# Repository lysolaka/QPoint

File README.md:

# QPoint

This is a medicore BJT measurement device. It does not use SMUs, negative voltages, and other fancy things. The focus of this project was to learn analog circuits and use them in something (hopefully fun).

# License

This project is licensed under the GNU General Public License v3.0 or later (at your option).

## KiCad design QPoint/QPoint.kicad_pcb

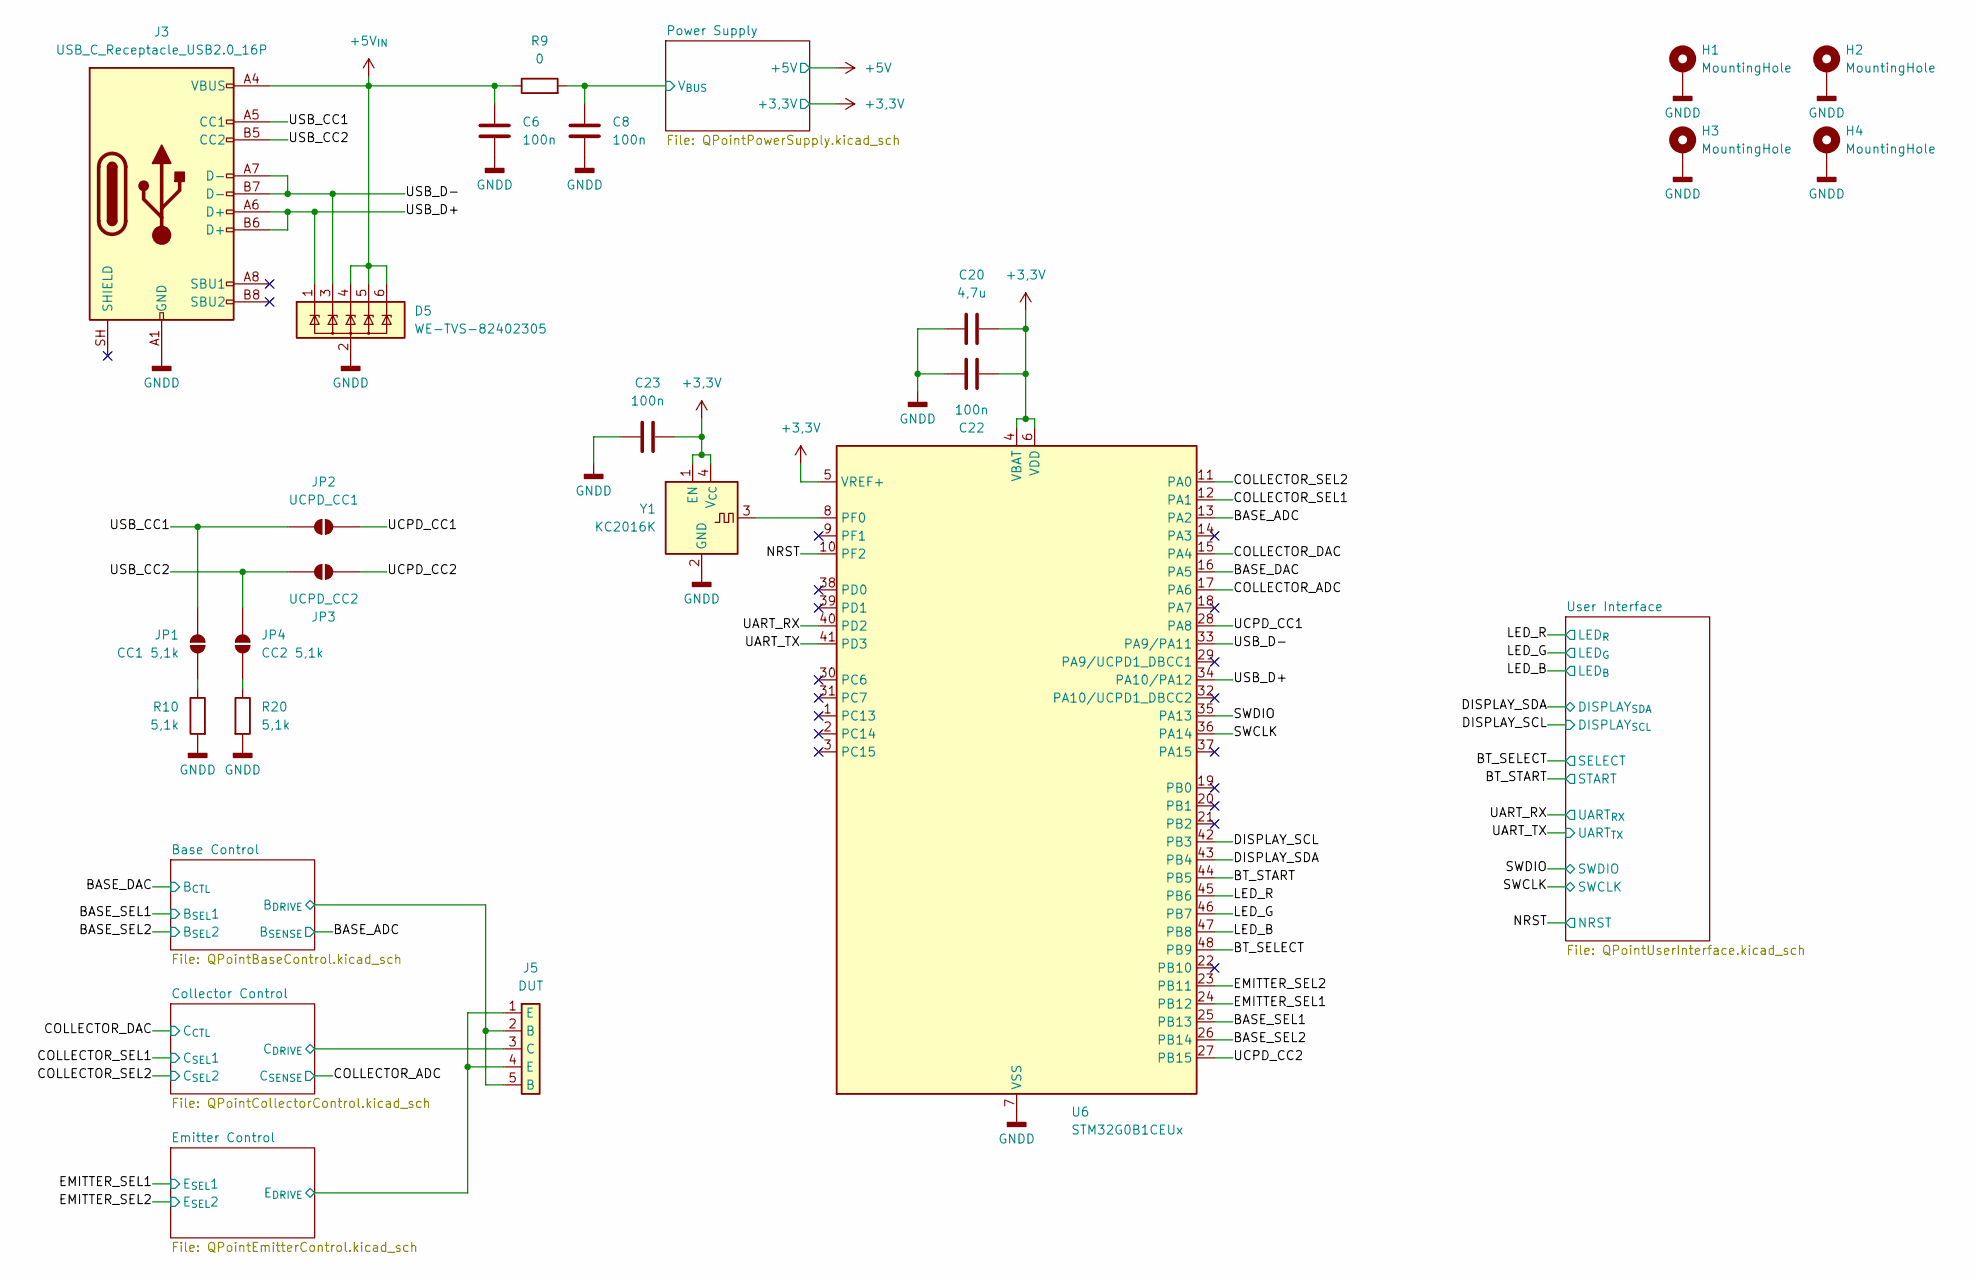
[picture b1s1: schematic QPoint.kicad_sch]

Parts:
C6, C8, C22, C23: 100n; C_0603_1608Metric_Pad1.08x0.95mm_HandSolder
C20: 4,7u; C_0805_2012Metric_Pad1.18x1.45mm_HandSolder
D5: WE-TVS-82402305; SOT-23-6_Handsoldering
H1, H2, H3, H4: MountingHole; MountingHole_3.2mm_M3_Pad
J3: USB_C_Receptacle_USB2.0_16P; USB_C_Receptacle_GCT_USB4085
J5: DUT; Connector_DUT_P2.54mm
JP1: CC1 5,1k; SolderJumper-2_P1.3mm_Open_TrianglePad1.0x1.5mm
JP2: UCPD_CC1; SolderJumper-2_P1.3mm_Open_TrianglePad1.0x1.5mm
JP3: UCPD_CC2; SolderJumper-2_P1.3mm_Open_TrianglePad1.0x1.5mm
JP4: CC2 5,1k; SolderJumper-2_P1.3mm_Open_TrianglePad1.0x1.5mm
R9: 0; R_0805_2012Metric_Pad1.20x1.40mm_HandSolder
R10, R20: 5,1k; R_0603_1608Metric_Pad0.98x0.95mm_HandSolder
U6: STM32G0B1CEUx; QFN-48-1EP_7x7mm_P0.5mm_EP5.6x5.6mm_GroundingVias
Y1: KC2016K; Oscillator_SMD_KC2016K_2.0x.16mm

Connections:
+3,3V: C20.2, C22.2, C23.2, U6.4 (VBAT), U6.5 (VREF+), U6.6 (VDD), Y1.1 (EN), Y1.4 (V_{CC}); also elsewhere on the board
+5V_{IN}: C6.1, D5.4, D5.5, D5.6, J3.A4 (VBUS), J3.A9 (VBUS), J3.B4 (VBUS), J3.B9 (VBUS), R9.1
/BASE_ADC: U6.13 (PA2); also elsewhere on the board
/BASE_DAC: U6.16 (PA5); also elsewhere on the board
/BASE_SEL1: U6.25 (PB13); also elsewhere on the board
/BASE_SEL2: U6.26 (PB14); also elsewhere on the board
/BT_SELECT: U6.48 (PB9); also elsewhere on the board
/BT_START: U6.44 (PB5); also elsewhere on the board
/Base Control/B_{DRIVE}: J5.2 (B), J5.5 (B); also elsewhere on the board
/COLLECTOR_ADC: U6.17 (PA6); also elsewhere on the board
/COLLECTOR_DAC: U6.15 (PA4); also elsewhere on the board
/COLLECTOR_SEL1: U6.12 (PA1); also elsewhere on the board
/COLLECTOR_SEL2: U6.11 (PA0); also elsewhere on the board
/Collector Control/C_{DRIVE}: J5.3 (C); also elsewhere on the board
/DISPLAY_SCL: U6.42 (PB3); also elsewhere on the board
/DISPLAY_SDA: U6.43 (PB4); also elsewhere on the board
/EMITTER_SEL1: U6.24 (PB12); also elsewhere on the board
/EMITTER_SEL2: U6.23 (PB11); also elsewhere on the board
/Emitter Control/E_{DRIVE}: J5.1 (E), J5.4 (E); also elsewhere on the board
/LED_B: U6.47 (PB8); also elsewhere on the board
/LED_G: U6.46 (PB7); also elsewhere on the board
/LED_R: U6.45 (PB6); also elsewhere on the board
/NRST: U6.10 (PF2); also elsewhere on the board
/Power Supply/V_{BUS}: C8.1, R9.2; also elsewhere on the board
/SWCLK: U6.36 (PA14); also elsewhere on the board
/SWDIO: U6.35 (PA13); also elsewhere on the board
/UART_RX: U6.40 (PD2); also elsewhere on the board
/UART_TX: U6.41 (PD3); also elsewhere on the board
/UCPD_CC1: JP2.2 (B), U6.28 (PA8)
/UCPD_CC2: JP3.2 (B), U6.27 (PB15)
/USB_CC1: J3.A5 (CC1), JP1.1 (A), JP2.1 (A)
/USB_CC2: J3.B5 (CC2), JP3.1 (A), JP4.1 (A)
/USB_D+: D5.1, J3.A6 (D+), J3.B6 (D+), U6.34 (PA10/PA12)
/USB_D-: D5.3, J3.A7 (D-), J3.B7 (D-), U6.33 (PA9/PA11)
GNDD: C6.2, C8.2, C20.1, C22.1, C23.1, D5.2, H1.1 (1_1), H2.1 (1_1), H3.1 (1_1), H4.1 (1_1), J3.A1 (GND), J3.A12 (GND), J3.B1 (GND), J3.B12 (GND), R10.2, R20.2, U6.7 (VSS), U6.49 (VSS), Y1.2 (GND); also elsewhere on the board
unnamed: JP1.2 (B), R10.1
unnamed: JP4.2 (B), R20.1
unnamed: U6.8 (PF0), Y1.3

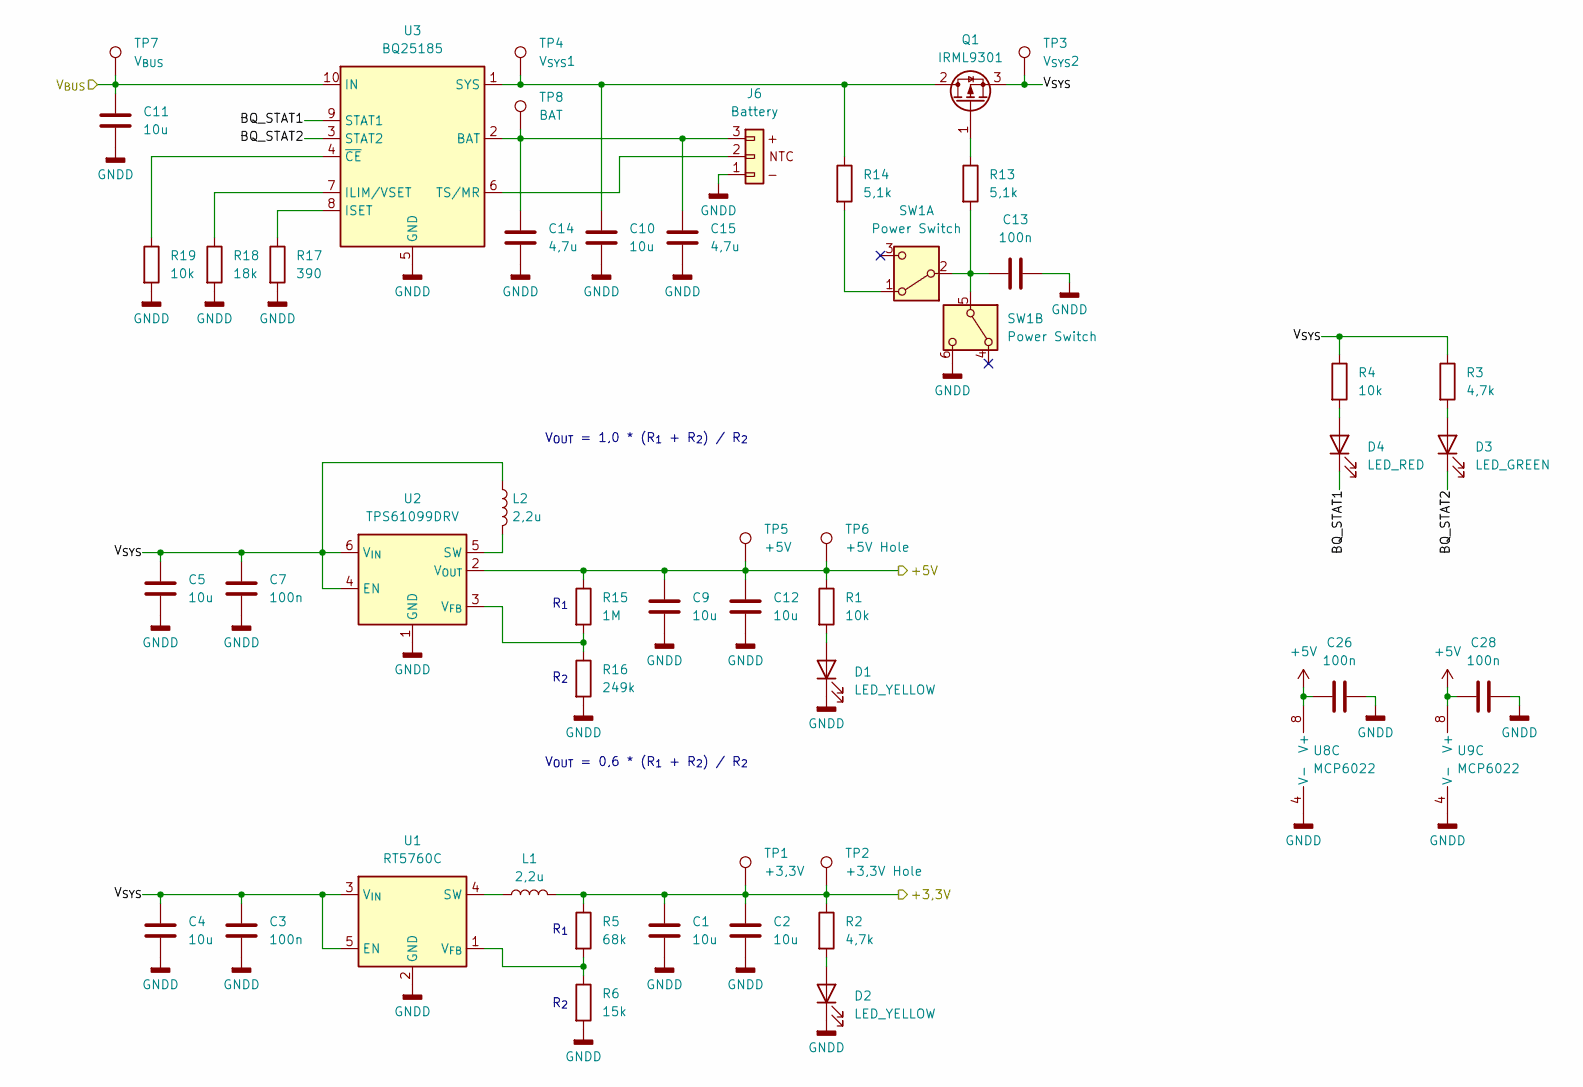
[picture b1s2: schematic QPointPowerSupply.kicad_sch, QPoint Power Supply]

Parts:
C1, C2, C4, C5, C9, C10, C11, C12: 10u; C_0805_2012Metric_Pad1.18x1.45mm_HandSolder
C3, C7, C13, C26, C28: 100n; C_0603_1608Metric_Pad1.08x0.95mm_HandSolder
C14, C15: 4,7u; C_0805_2012Metric_Pad1.18x1.45mm_HandSolder
D1, D2: LED_YELLOW; LED_0805_2012Metric_Pad1.15x1.40mm_HandSolder
D3: LED_GREEN; LED_0805_2012Metric_Pad1.15x1.40mm_HandSolder
D4: LED_RED; LED_0805_2012Metric_Pad1.15x1.40mm_HandSolder
J6: Battery; Molex_PicoBlade_53048-0310_1x03_P1.25mm_Horizontal
L1, L2: 2,2u; L_Sunlord_MWSA0503S
Q1: IRML9301; SOT-23_Handsoldering
R1, R4, R19: 10k; R_0603_1608Metric_Pad0.98x0.95mm_HandSolder
R2, R3: 4,7k; R_0603_1608Metric_Pad0.98x0.95mm_HandSolder
R5: 68k; R_0603_1608Metric_Pad0.98x0.95mm_HandSolder
R6: 15k; R_0603_1608Metric_Pad0.98x0.95mm_HandSolder
R13, R14: 5,1k; R_0603_1608Metric_Pad0.98x0.95mm_HandSolder
R15: 1M; R_0603_1608Metric_Pad0.98x0.95mm_HandSolder
R16: 249k; R_0603_1608Metric_Pad0.98x0.95mm_HandSolder
R17: 390; R_0603_1608Metric_Pad0.98x0.95mm_HandSolder
R18: 18k; R_0603_1608Metric_Pad0.98x0.95mm_HandSolder
SW1: Power Switch; SW_Push_PB07_7x7mm
TP1: +3,3V; TestPoint_Pad_D2.0mm
TP2: +3,3V Hole; TestPoint_THTPad_D2.0mm_Drill1.0mm
TP3: V_{SYS}2; TestPoint_Pad_D2.0mm
TP4: V_{SYS}1; TestPoint_Pad_D2.0mm
TP5: +5V; TestPoint_Pad_D2.0mm
TP6: +5V Hole; TestPoint_THTPad_D2.0mm_Drill1.0mm
TP7: V_{BUS}; TestPoint_Pad_D2.0mm
TP8: BAT; TestPoint_Pad_D2.0mm
U1: RT5760C; SOT-563_Handsoldering
U2: TPS61099DRV; WSON-6-1EP_2x2mm_P0.65mm_EP1x1.6mm_GroundingVias
U3: BQ25185; Texas_DLH0010A_WSON-10-1EP_2.2x2mm_P0.4mm_EP0.9x1.5mm_Groun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
U8, U9: MCP6022; SOIC-8_3.9x4.9mm_P1.27mm_Handsoldering

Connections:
+3,3V: C1.1, C2.1, L1.2, R2.1, R5.1, TP1.1 (1_1), TP2.1 (1_1); also elsewhere on the board
+5V: C9.1, C12.1, C26.1, C28.1, R1.1, R15.1, TP5.1 (1_1), TP6.1 (1_1), U2.2 (V_{OUT}), U8.8 (V+), U9.8 (V+); also elsewhere on the board
/Power Supply/BQ_STAT1: D4.1 (K), U3.9 (STAT1)
/Power Supply/BQ_STAT2: D3.1 (K), U3.3 (STAT2)
/Power Supply/V_{BUS}: C11.1, TP7.1 (1_1), U3.10 (IN); also elsewhere on the board
/Power Supply/V_{SYS}: C3.1, C4.1, C5.1, C7.1, L2.1, Q1.3 (S), R3.1, R4.1, TP3.1 (1_1), U1.3 (V_{IN}), U1.5 (EN), U2.4 (EN), U2.6 (V_{IN})
GNDD: C1.2, C2.2, C3.2, C4.2, C5.2, C7.2, C9.2, C10.2, C11.2, C12.2, C13.2, C14.2, C15.2, C26.2, C28.2, D1.1 (K), D2.1 (K), J6.1, R6.2, R16.2, R17.2, R18.2, R19.2, SW1.6 (C), U1.2 (GND), U2.1 (GND), U2.7 (GND), U3.5 (GND), U3.11 (TP), U8.4 (V-), U9.4 (V-); also elsewhere on the board
unnamed: D1.2 (A), R1.2
unnamed: D2.2 (A), R2.2
unnamed: D3.2 (A), R3.2
unnamed: D4.2 (A), R4.2
unnamed: C10.1, Q1.2 (D), R14.1, TP4.1 (1_1), U3.1 (SYS)
unnamed: Q1.1 (G), R13.1
unnamed: R14.2, SW1.1 (A)
unnamed: C13.1, R13.2, SW1.2 (B), SW1.5 (B)
unnamed: L1.1, U1.4 (SW)
unnamed: R5.2, R6.1, U1.1 (V_{FB})
unnamed: L2.2, U2.5 (SW)
unnamed: R15.2, R16.1, U2.3 (V_{FB})
unnamed: C14.1, C15.1, J6.3, TP8.1 (1_1), U3.2 (BAT)
unnamed: R18.1, U3.7 (ILIM/VSET)
unnamed: R17.1, U3.8 (ISET)
unnamed: J6.2, U3.6 (TS/MR)
unnamed: R19.1, U3.4 (~CE)

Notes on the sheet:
R_{2}
V_{OUT} = 0,6 * (R_{1} + R_{2}) / R_{2}
R_{1}
V_{OUT} = 1,0 * (R_{1} + R_{2}) / R_{2}

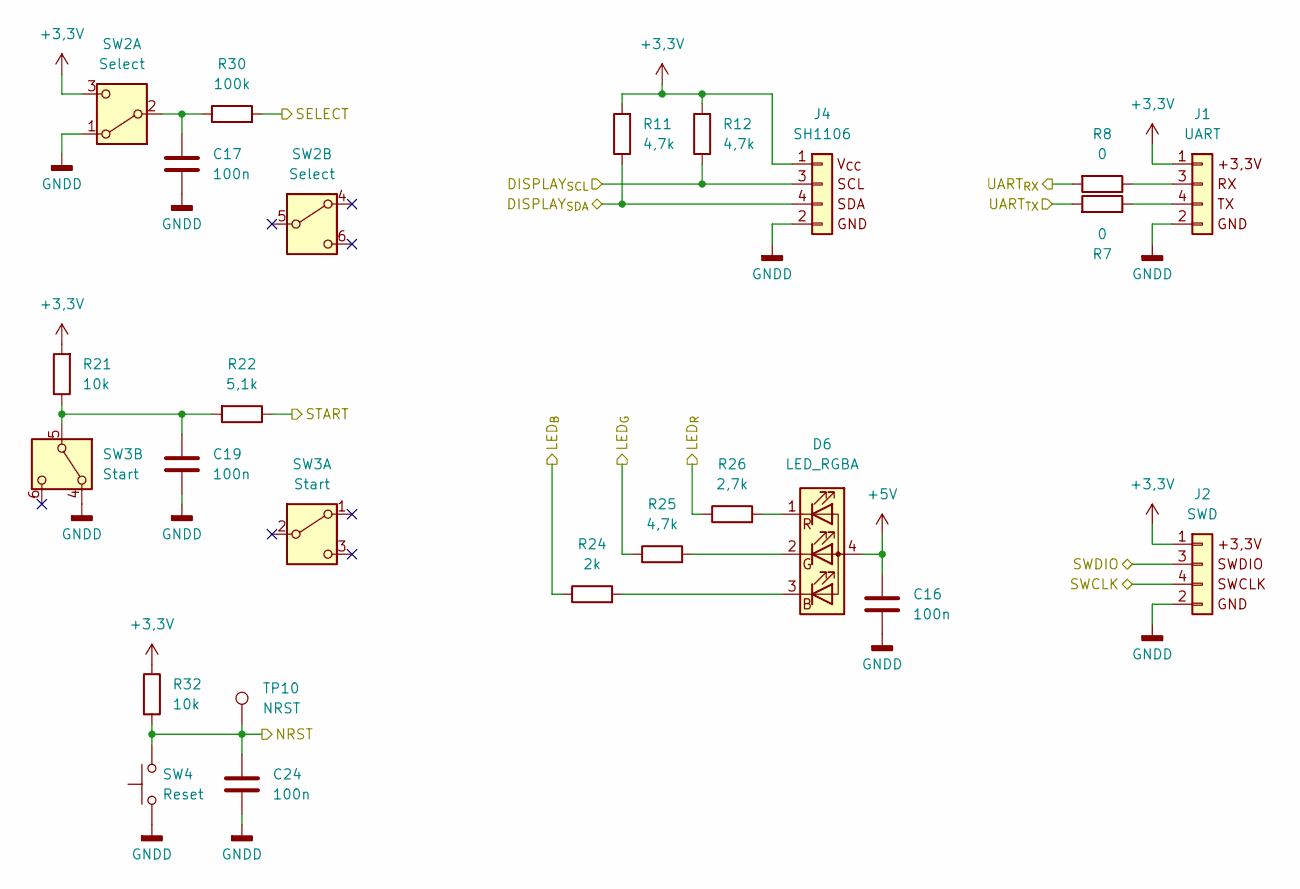
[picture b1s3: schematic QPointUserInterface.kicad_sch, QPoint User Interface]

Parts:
C16, C17, C19, C24: 100n; C_0603_1608Metric_Pad1.08x0.95mm_HandSolder
D6: LED_RGBA; LED_LiteOn_LTST-C19HE1WT
J1: UART; Connector_UART_P2.54mm
J2: SWD; Connector_SWD_P2.54mm
J4: SH1106; Connector_SH1106_P2.54mm
R7, R8: 0; R_0805_2012Metric_Pad1.20x1.40mm_HandSolder
R11, R12, R25: 4,7k; R_0603_1608Metric_Pad0.98x0.95mm_HandSolder
R21, R32: 10k; R_0603_1608Metric_Pad0.98x0.95mm_HandSolder
R22: 5,1k; R_0603_1608Metric_Pad0.98x0.95mm_HandSolder
R24: 2k; R_0603_1608Metric_Pad0.98x0.95mm_HandSolder
R26: 2,7k; R_0603_1608Metric_Pad0.98x0.95mm_HandSolder
R30: 100k; R_0603_1608Metric_Pad0.98x0.95mm_HandSolder
SW2: Select; SW_Push_PB07_7x7mm
SW3: Start; SW_Push_PB07_7x7mm
SW4: Reset; SW_Push_SPST_China
TP10: NRST; TestPoint_THTPad_D2.0mm_Drill1.0mm

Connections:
+3,3V: J1.1, J2.1, J4.1, R11.2, R12.2, R21.2, R32.1, SW2.3 (C); also elsewhere on the board
+5V: C16.1, D6.4 (A); also elsewhere on the board
/BT_SELECT: R30.2; also elsewhere on the board
/BT_START: R22.1; also elsewhere on the board
/DISPLAY_SCL: J4.3, R12.1; also elsewhere on the board
/DISPLAY_SDA: J4.4, R11.1; also elsewhere on the board
/LED_B: R24.1; also elsewhere on the board
/LED_G: R25.1; also elsewhere on the board
/LED_R: R26.1; also elsewhere on the board
/NRST: C24.1, R32.2, SW4.2, TP10.1 (1_1); also elsewhere on the board
/SWCLK: J2.4; also elsewhere on the board
/SWDIO: J2.3; also elsewhere on the board
/UART_RX: R8.2; also elsewhere on the board
/UART_TX: R7.2; also elsewhere on the board
GNDD: C16.2, C17.2, C19.2, C24.2, J1.2, J2.2, J4.2, SW2.1 (A), SW3.4 (A), SW4.1; also elsewhere on the board
unnamed: D6.3 (BK), R24.2
unnamed: D6.2 (GK), R25.2
unnamed: D6.1 (RK), R26.2
unnamed: J1.3, R8.1
unnamed: J1.4, R7.1
unnamed: C17.1, R30.1, SW2.2 (B)
unnamed: C19.1, R21.1, R22.2, SW3.5 (B)

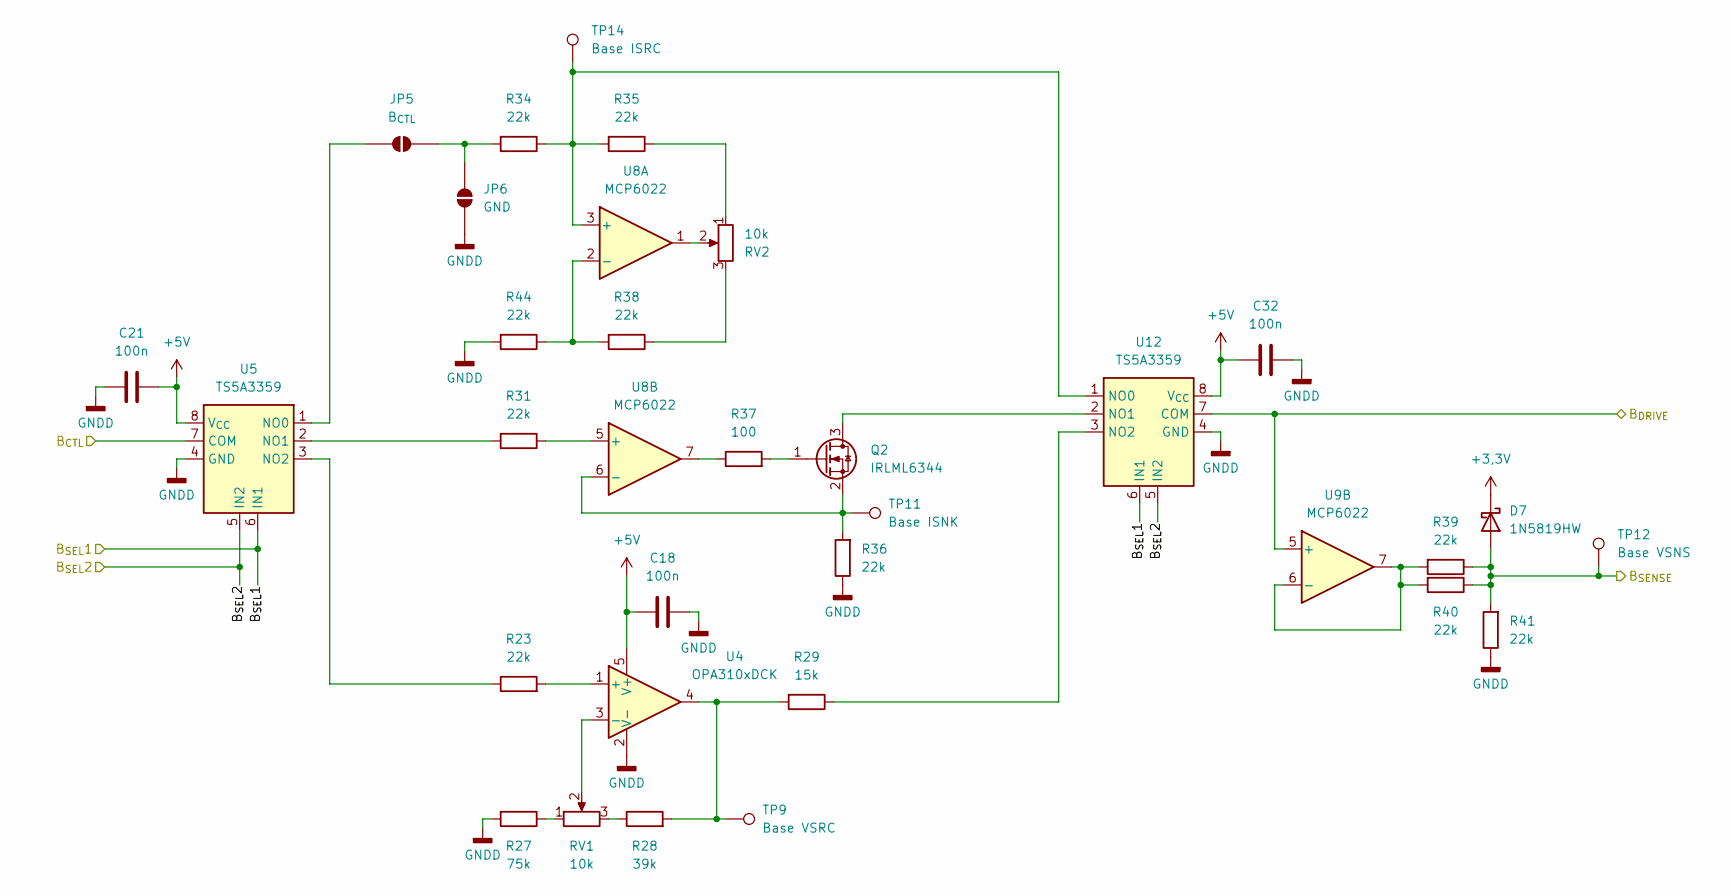
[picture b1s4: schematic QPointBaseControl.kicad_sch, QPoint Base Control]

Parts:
C18, C21, C32: 100n; C_0603_1608Metric_Pad1.08x0.95mm_HandSolder
D7: 1N5819HW; D_SOD-123_Handsoldering
JP5: B_{CTL}; SolderJumper-2_P1.3mm_Open_TrianglePad1.0x1.5mm
JP6: GND; SolderJumper-2_P1.3mm_Open_TrianglePad1.0x1.5mm
Q2: IRLML6344; SOT-23_Handsoldering
R23, R31, R34, R35, R36, R38, R39, R40, R41, R44: 22k; R_0603_1608Metric_Pad0.98x0.95mm_HandSolder
R27: 75k; R_0603_1608Metric_Pad0.98x0.95mm_HandSolder
R28: 39k; R_0603_1608Metric_Pad0.98x0.95mm_HandSolder
R29: 15k; R_0603_1608Metric_Pad0.98x0.95mm_HandSolder
R37: 100; R_0603_1608Metric_Pad0.98x0.95mm_HandSolder
RV1, RV2: 10k; Potentiometer_Bourns_3296X_Horizontal
TP9: Base VSRC; TestPoint_Pad_D2.0mm
TP11: Base ISNK; TestPoint_Pad_D2.0mm
TP12: Base VSNS; TestPoint_Pad_D2.0mm
TP14: Base ISRC; TestPoint_Pad_D2.0mm
U4: OPA310xDCK; SOT-353_SC-70-5_Handsoldering
U5, U12: TS5A3359; VSSOP-8_2.3x2mm_P0.5mm_Handsoldering
U8, U9: MCP6022; SOIC-8_3.9x4.9mm_P1.27mm_Handsoldering

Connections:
+3,3V: D7.1 (K); also elsewhere on the board
+5V: C18.1, C21.2, C32.2, U4.5 (V+), U5.8 (V_{CC}), U12.8 (V_{CC}); also elsewhere on the board
/BASE_ADC: D7.2 (A), R39.1, R40.1, R41.2, TP12.1 (1_1); also elsewhere on the board
/BASE_DAC: U5.7 (COM); also elsewhere on the board
/BASE_SEL1: U5.6 (IN1), U12.6 (IN1); also elsewhere on the board
/BASE_SEL2: U5.5 (IN2), U12.5 (IN2); also elsewhere on the board
/Base Control/B_{DRIVE}: U9.5 (+), U12.7 (COM); also elsewhere on the board
GNDD: C18.2, C21.1, C32.1, JP6.1 (A), R27.2, R36.1, R41.1, R44.2, U4.2 (V-), U5.4 (GND), U12.4 (GND); also elsewhere on the board
unnamed: JP5.1 (A), U5.1 (NO0)
unnamed: JP5.2 (B), JP6.2 (B), R34.2
unnamed: Q2.3 (D), U12.2 (NO1)
unnamed: Q2.1 (G), R37.2
unnamed: Q2.2 (S), R36.2, TP11.1 (1_1), U8.6 (-)
unnamed: R27.1, RV1.1
unnamed: R28.1, RV1.3
unnamed: R28.2, R29.2, TP9.1 (1_1), U4.4
unnamed: R35.1, RV2.1
unnamed: R37.1, U8.7
unnamed: R38.1, RV2.3
unnamed: RV2.2, U8.1
unnamed: R23.2, U4.1 (+)
unnamed: RV1.2, U4.3 (-)
unnamed: R31.2, U5.2 (NO1)
unnamed: R23.1, U5.3 (NO2)
unnamed: R38.2, R44.1, U8.2 (-)
unnamed: R31.1, U8.5 (+)
unnamed: R39.2, R40.2, U9.6 (-), U9.7
unnamed: R34.1, R35.2, TP14.1 (1_1), U8.3 (+), U12.1 (NO0)
unnamed: R29.1, U12.3 (NO2)

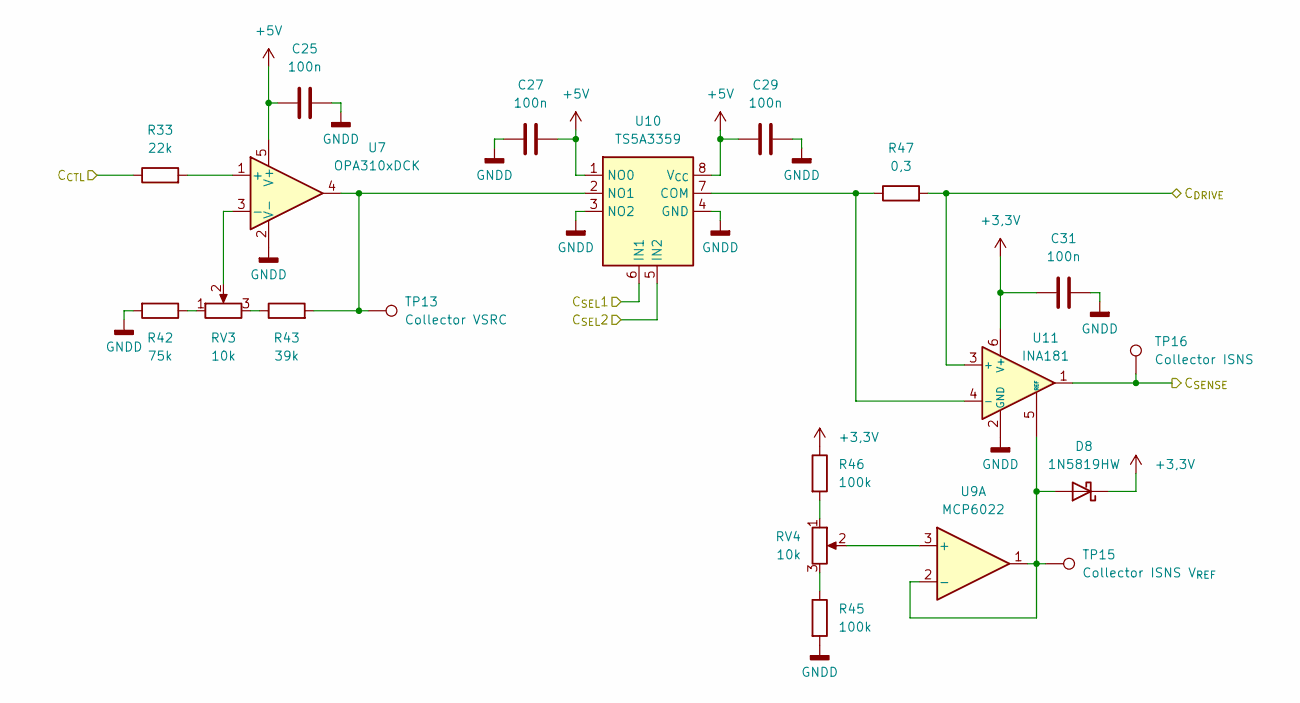
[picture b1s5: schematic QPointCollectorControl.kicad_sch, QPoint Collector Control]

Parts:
C25, C27, C29, C31: 100n; C_0603_1608Metric_Pad1.08x0.95mm_HandSolder
D8: 1N5819HW; D_SOD-123_Handsoldering
R33: 22k; R_0603_1608Metric_Pad0.98x0.95mm_HandSolder
R42: 75k; R_0603_1608Metric_Pad0.98x0.95mm_HandSolder
R43: 39k; R_0603_1608Metric_Pad0.98x0.95mm_HandSolder
R45, R46: 100k; R_0603_1608Metric_Pad0.98x0.95mm_HandSolder
R47: 0,3; R_0805_2012Metric_Pad1.20x1.40mm_HandSolder
RV3, RV4: 10k; Potentiometer_Bourns_3296X_Horizontal
TP13: Collector VSRC; TestPoint_Pad_D2.0mm
TP15: Collector ISNS V_{REF}; TestPoint_Pad_D2.0mm
TP16: Collector ISNS; TestPoint_Pad_D2.0mm
U7: OPA310xDCK; SOT-353_SC-70-5_Handsoldering
U9: MCP6022; SOIC-8_3.9x4.9mm_P1.27mm_Handsoldering
U10: TS5A3359; VSSOP-8_2.3x2mm_P0.5mm_Handsoldering
U11: INA181; SOT-23-6_Handsoldering

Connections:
+3,3V: C31.2, D8.1 (K), R46.1, U11.6 (V+); also elsewhere on the board
+5V: C25.1, C27.2, C29.2, U7.5 (V+), U10.1 (NO0), U10.8 (V_{CC}); also elsewhere on the board
/COLLECTOR_ADC: TP16.1 (1_1), U11.1; also elsewhere on the board
/COLLECTOR_DAC: R33.1; also elsewhere on the board
/COLLECTOR_SEL1: U10.6 (IN1); also elsewhere on the board
/COLLECTOR_SEL2: U10.5 (IN2); also elsewhere on the board
/Collector Control/C_{DRIVE}: R47.2, U11.3 (+); also elsewhere on the board
GNDD: C25.2, C27.1, C29.1, C31.1, R42.2, R45.2, U7.2 (V-), U10.3 (NO2), U10.4 (GND), U11.2 (GND); also elsewhere on the board
unnamed: D8.2 (A), TP15.1 (1_1), U9.1, U9.2 (-), U11.5 (REF)
unnamed: R42.1, RV3.1
unnamed: R43.1, RV3.3
unnamed: R45.1, RV4.3
unnamed: R46.2, RV4.1
unnamed: R33.2, U7.1 (+)
unnamed: RV3.2, U7.3 (-)
unnamed: RV4.2, U9.3 (+)
unnamed: R47.1, U10.7 (COM), U11.4 (-)
unnamed: R43.2, TP13.1 (1_1), U7.4, U10.2 (NO1)

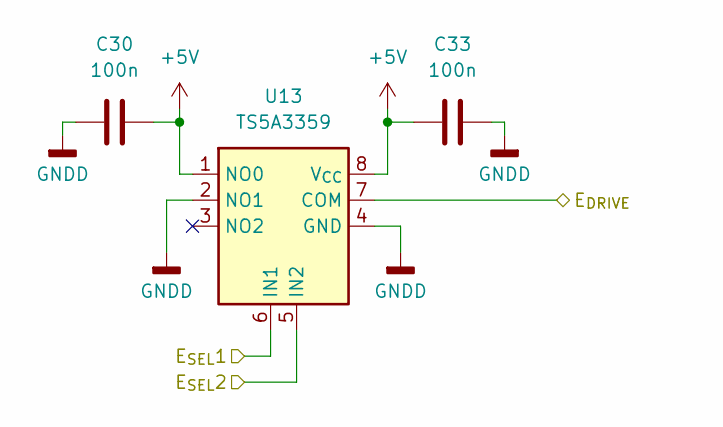
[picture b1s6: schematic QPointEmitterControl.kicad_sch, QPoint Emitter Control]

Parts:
C30, C33: 100n; C_0603_1608Metric_Pad1.08x0.95mm_HandSolder
U13: TS5A3359; VSSOP-8_2.3x2mm_P0.5mm_Handsoldering

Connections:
+5V: C30.2, C33.2, U13.1 (NO0), U13.8 (V_{CC}); also elsewhere on the board
/EMITTER_SEL1: U13.6 (IN1); also elsewhere on the board
/EMITTER_SEL2: U13.5 (IN2); also elsewhere on the board
/Emitter Control/E_{DRIVE}: U13.7 (COM); also elsewhere on the board
GNDD: C30.1, C33.1, U13.2 (NO1), U13.4 (GND); also elsewhere on the board

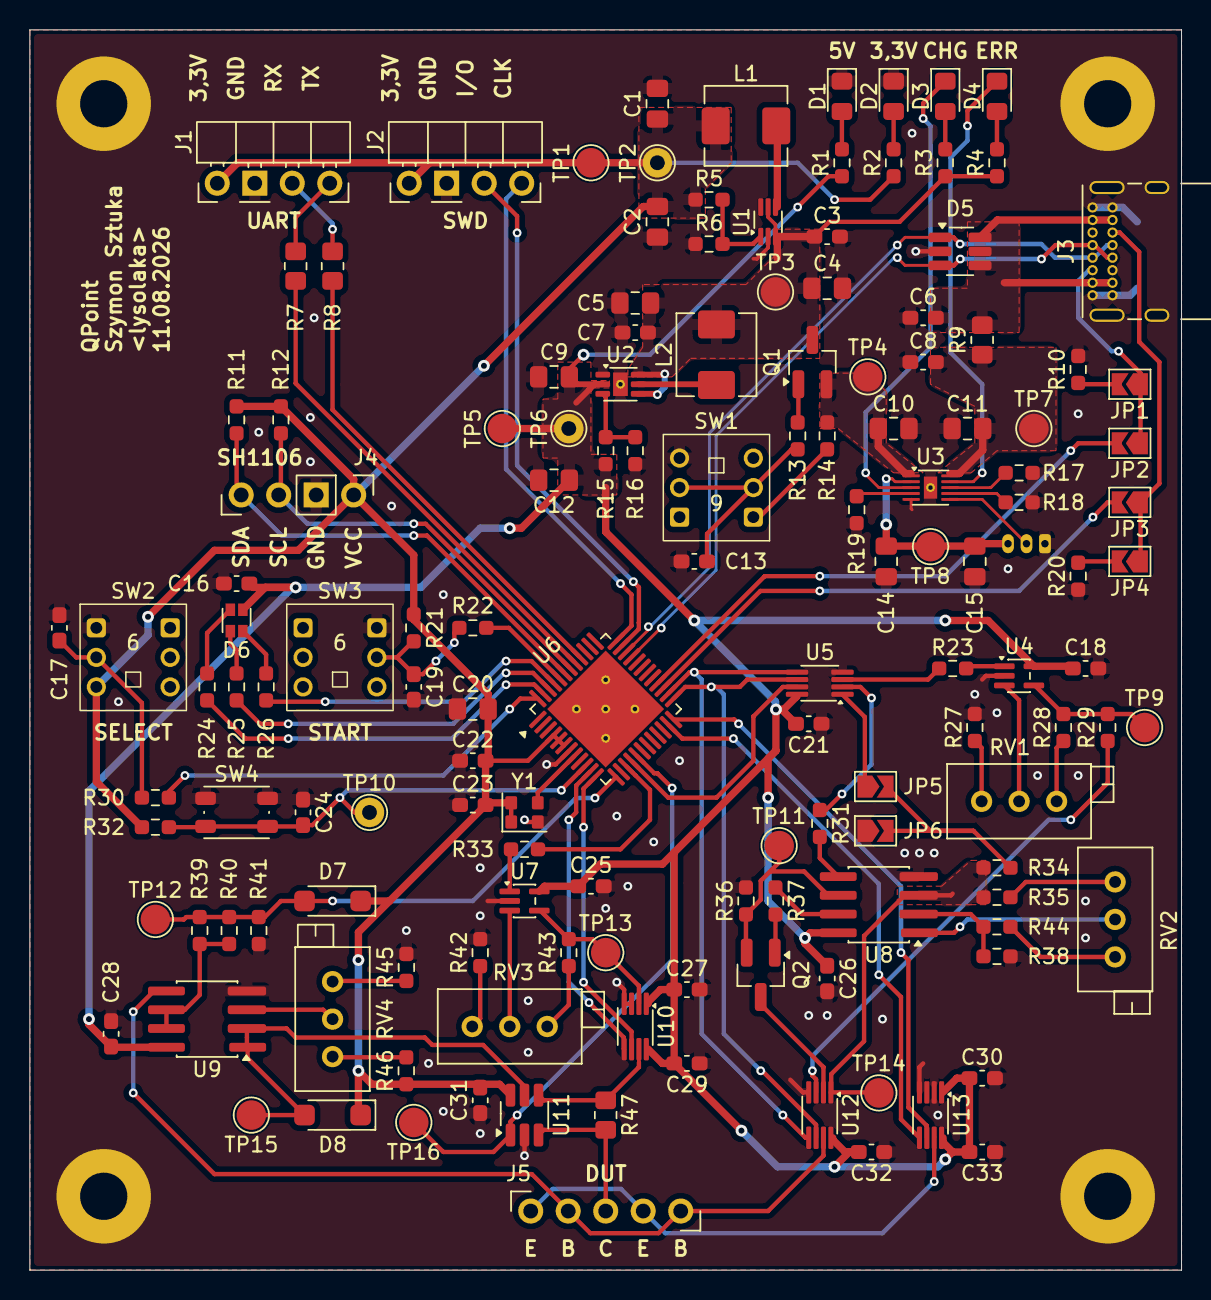
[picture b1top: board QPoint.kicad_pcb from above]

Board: 2 copper layers, 78.0 x 84.0 mm, 146 parts (1 on the bottom side), 97 nets.

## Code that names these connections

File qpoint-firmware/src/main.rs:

#![no_std]
#![no_main]

use defmt_rtt as _;
use panic_probe as _;

use embassy_executor::Spawner;

use embassy_stm32::{Peri, peripherals};
use embassy_stm32::{dma, exti, i2c, usb};

mod communication;
mod config;
mod display;
mod led;
mod measurement;
mod ui;
pub mod util;

use crate::util::color;
use crate::util::sync::RGB_LED_S;

assign_resources::assign_resources! {
    display: DisplayResources {
        i2c: I2C2,
        tx_dma: DMA1_CH2,
        rx_dma: DMA1_CH3,
        scl: PB3,
        sda: PB4,
    },
    led: LedResources {
        r: PB6,
        g: PB7,
        b: PB8,
        tim: TIM4,
    },
    measurement: MeasurementResources {
        dac: DAC1,
        adc: ADC1,
        dma: DMA1_CH1,
        base_sel1: PB13,
        base_sel2: PB14,
        base_dac: PA5,
        base_adc: PA2,
        collector_sel1: PA1,
        collector_sel2: PA0,
        collector_dac: PA4,
        collector_adc: PA6,
        emitter_sel1: PB12,
        emitter_sel2: PB11,
    },
    ui: UiResources {
        start_pin: PB5,
        start_exti: EXTI5,
        select_pin: PB9,
        select_exti: EXTI9,
    }
    usb: UsbResources {
        usb: USB,
        dp: PA12,
        dm: PA11,
    }
}

embassy_stm32::bind_interrupts!(struct Interrupts {
    DMA1_CHANNEL1 => dma::InterruptHandler<peripherals::DMA1_CH1>;
    DMA1_CHANNEL2_3 => dma::InterruptHandler<peripherals::DMA1_CH2>, dma::InterruptHandler<peripherals::DMA1_CH3>;
    EXTI4_15 => exti::InterruptHandler<embassy_stm32::interrupt::typelevel::EXTI4_15>;
    I2C2_3 => i2c::EventInterruptHandler<peripherals::I2C2>, i2c::ErrorInterruptHandler<peripherals::I2C2>;
    USB_UCPD1_2 => usb::InterruptHandler<peripherals::USB>;
});

#[embassy_executor::main]
async fn main(spawner: Spawner) {
    let p = embassy_stm32::init(config::hal_config());
    let r = split_resources!(p);

    defmt::info!("Startup: OK!");
    defmt::debug!("Spawning tasks...");

    spawner.spawn(defmt::unwrap!(led::driver(r.led)));
    spawner.spawn(defmt::unwrap!(ui::driver(r.ui)));
    spawner.spawn(defmt::unwrap!(display::driver(r.display)));
    spawner.spawn(defmt::unwrap!(measurement::runner(r.measurement)));

    communication::start(spawner, r.usb);

    RGB_LED_S.signal(color::OK);

    defmt::info!("Tasks spawned: OK!");
    defmt::debug!("Yeilding to the executor...");
}
